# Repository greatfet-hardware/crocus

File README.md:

# Crocus
A GreatFET Neighbor for the 2.4 GHz wireless band.

Required KiCad dependency:

https://github.com/greatscottgadgets/gsg-kicad-lib

If you are using git, the preferred way to install gsg-kicad-lib is to use the
submodule:

```
git submodule init && git submodule update
```

# Background

Crocus is based on the Nordic RF nRF24L01+ and was inspired by [The Next Hope Badge](http://goodfet.sourceforge.net/hardware/nhb12/).

A notable capability of nRF24L01+ is 2 Mbps FSK.  Many 2.4 GHz wireless transceiver ICs (including the CC2400 on Ubertooth One) only support FSK up to 1 Mbps.  See [Promiscuity is the nRF24L01+'s Duty](http://travisgoodspeed.blogspot.com/2011/02/promiscuity-is-nrf24l01s-duty.html) for an excellent trick that can be done with Crocus.

## Usage Instructions

FIXME: We don't have any firmware yet, but we should implement capabilities similar to goodfet.nrf.

## Pin Usage

signal  | pin     | alt1  | alt2
--------|---------|-------|-----
SCK     | J1.38   | J2.32 |
COPI    | J1.39   | J2.30 |
CIPO    | J1.40   | J2.38 |
CSN     | via I2C | J1.37 | J1.29
CE      | via I2C | J2.9  | J2.21
SDA     | J2.39   |       |
SCL     | J2.40   |       |
INT     | J2.4    | J2.34 | J1.36

Alternative pins may be selected with solder jumpers.

## I2C Address

The default I2C address is 0x27.  Alternative addresses in the ranges 0x10-0x2F, 0x50-0x67, or 0x70-0x77 may be selected with solder jumpers.  Refer to the Crocus schematic and to the PCA9674 data sheet for details.

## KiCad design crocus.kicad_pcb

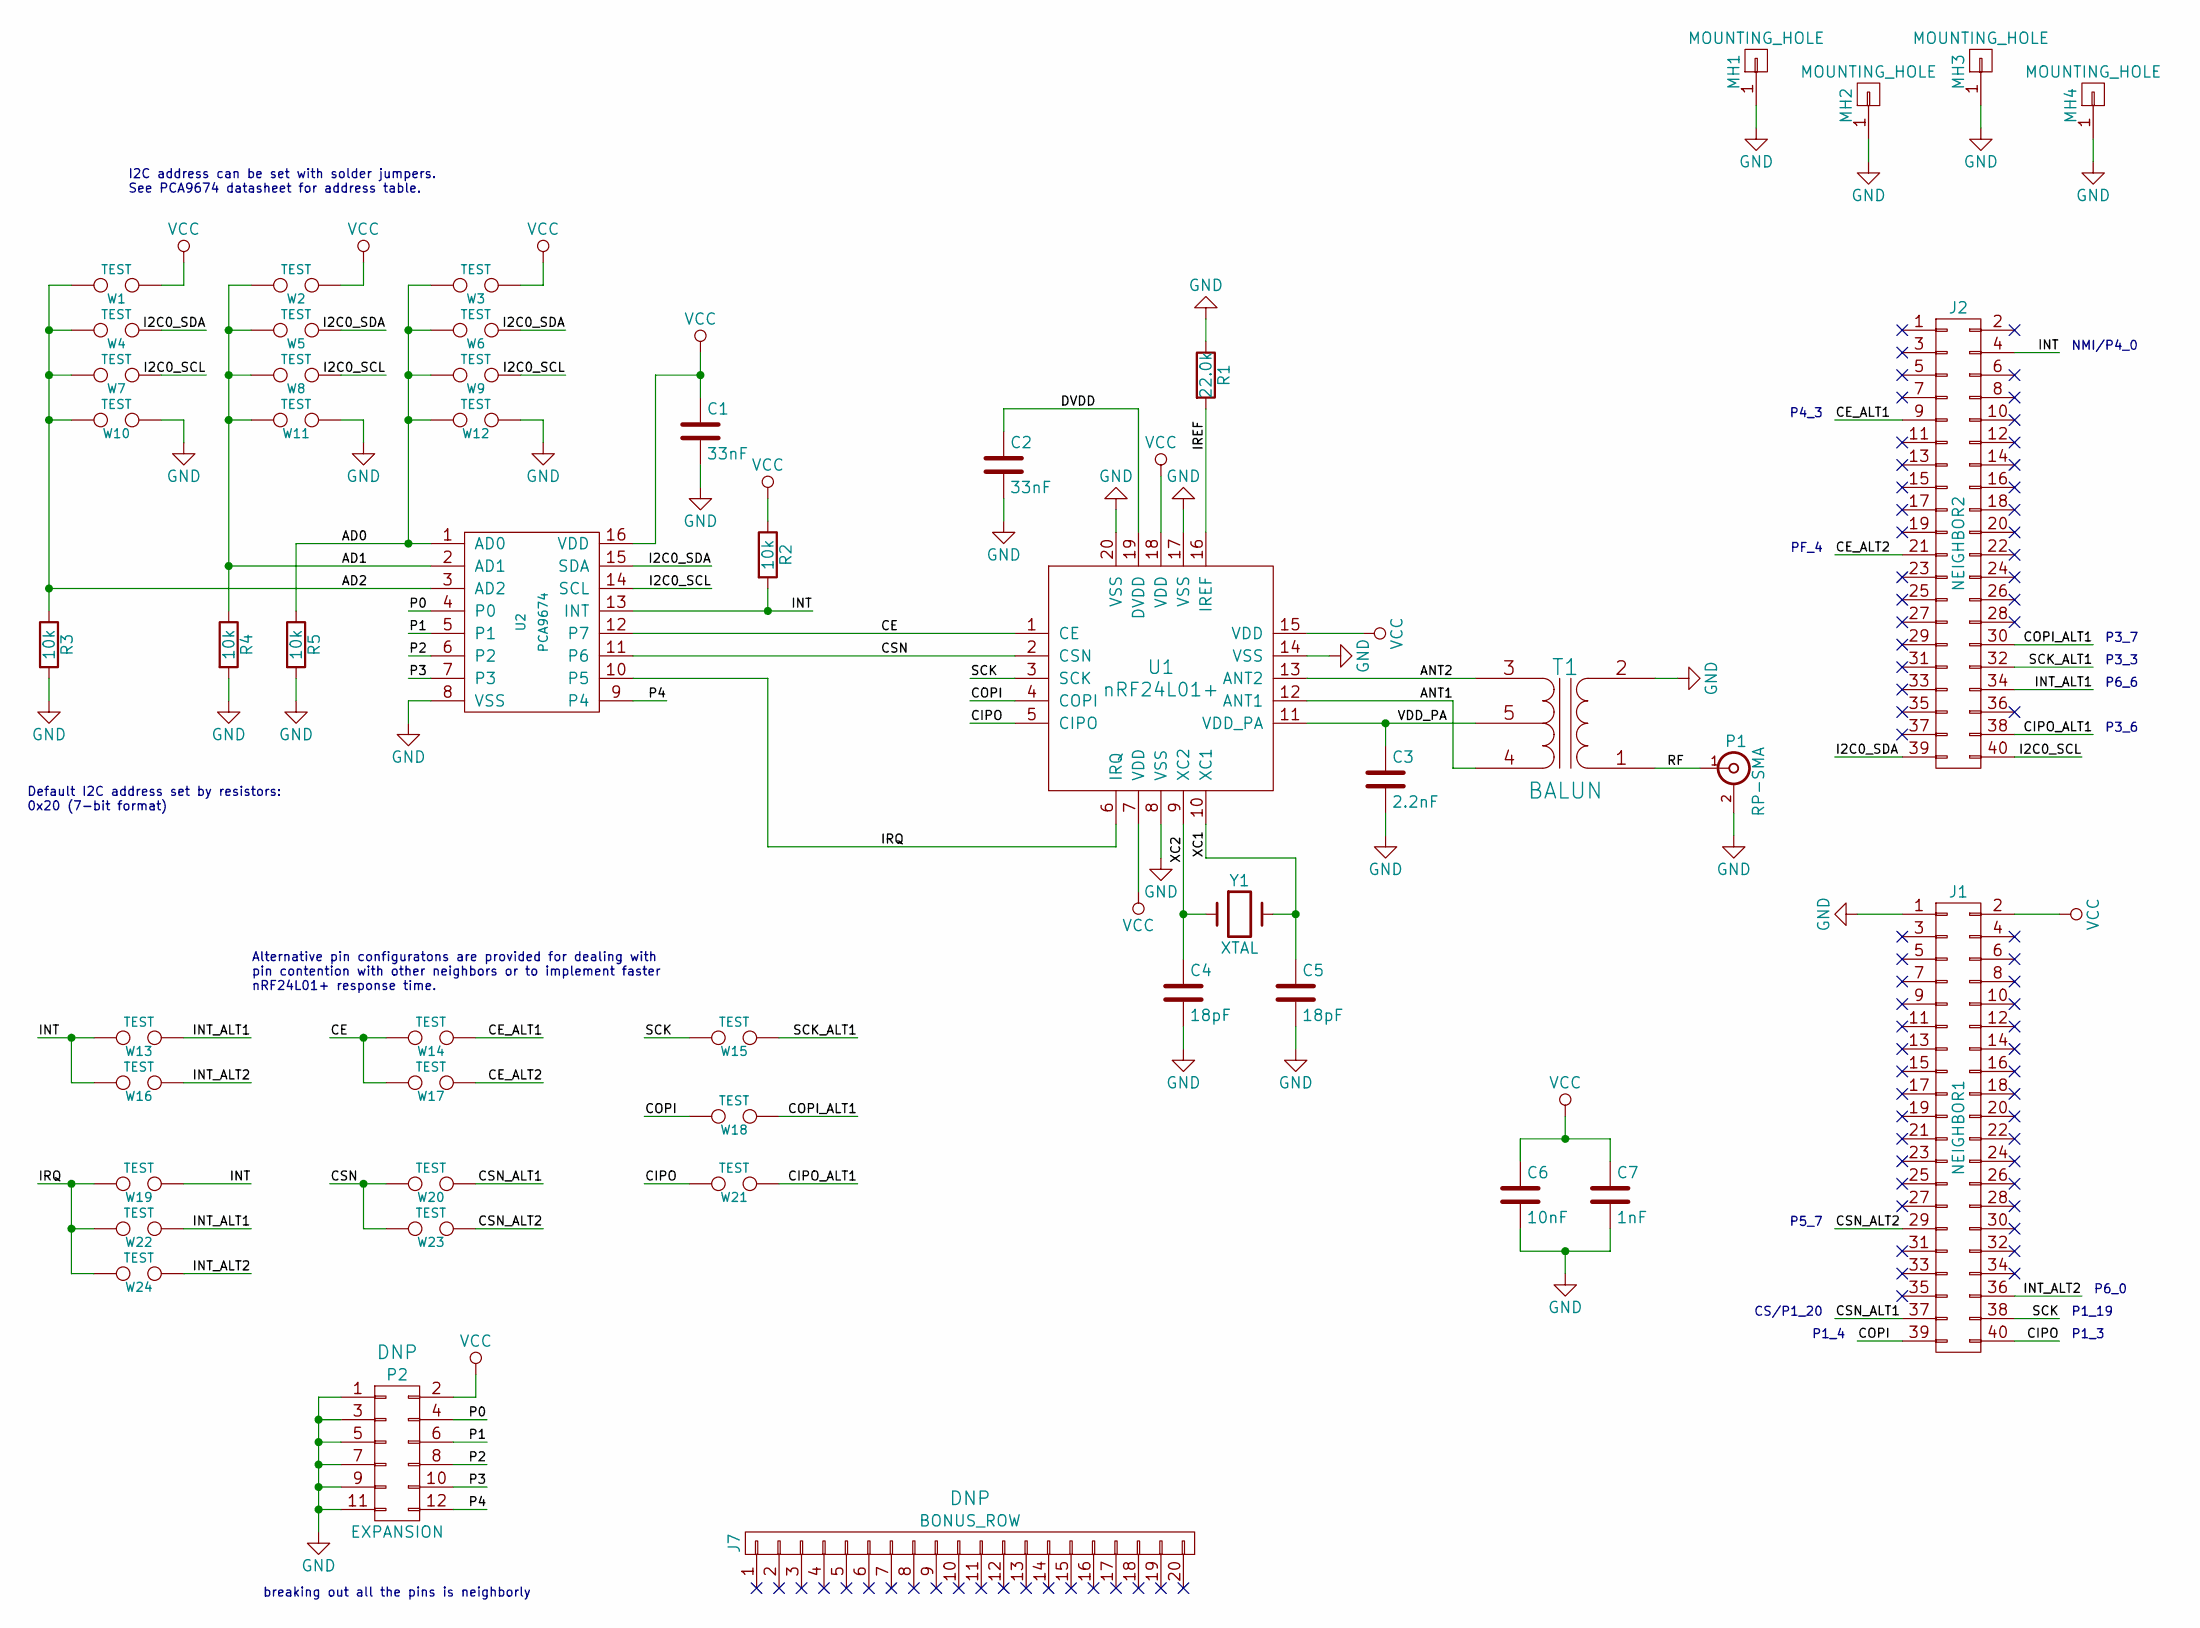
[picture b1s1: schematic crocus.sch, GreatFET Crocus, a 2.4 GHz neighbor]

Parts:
C1, C2: 33nF; 0603; Part Number CL10B333KB8SFNC
C3: 2.2nF; 0603; Part Number GRM188R71H222KA01D
C4, C5: 18pF; 0603; Part Number GRM1885C1H180JA01D
C6: 10nF; 0603; Part Number GRM188R71H103KA01D
C7: 1nF; 0603; Part Number GRM188R71H102KA01D
J1: NEIGHBOR1; HEADER-2x20; Part Number SSQ-120-23-G-D
J2: NEIGHBOR2; HEADER-2x20; Part Number SSQ-120-23-G-D
J7: BONUS_ROW; HEADER-1x20; Part Number SSQ-120-23-G-S
MH1, MH2, MH3, MH4: MOUNTING_HOLE; HOLE126MIL-COPPER
P1: RP-SMA; SMA-EDGE; Part Number CONREVSMA003.031
P2: EXPANSION; HEADER-2x6
R1: 22.0k; 0603; Part Number RMCF0603FT22K0
R2, R3, R4, R5: 10k; 0603; Part Number ERJ-3GEYJ103V
T1: BALUN; 2500BL14M100; Part Number 2450BM14A0002T
U1: nRF24L01+; QFN20-4; Part Number NRF24L01P-R7
U2: PCA9674; TSSOP16; Part Number PCA9674PW,118
W1, W2, W3, W4, W5, W6, W7, W8, W9, W10, W11, W12, W13, W14, W15, W16, W17, W18, W19, W20, W21, W22, W23, W24: TEST; 0603-JUMPER
Y1: XTAL; HC-49S; Part Number 9C-16.000MAAE-T

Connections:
/AD0: R5.1, U2.1 (AD0), W3.2, W6.2, W9.2, W12.2
/AD1: R4.1, U2.2 (AD1), W2.2, W5.2, W8.2, W11.2
/AD2: R3.1, U2.3 (AD2), W1.2, W4.2, W7.2, W10.2
/ANT1: T1.4 (PR2), U1.12 (ANT1)
/ANT2: T1.3 (PR1), U1.13 (ANT2)
/CE: U1.1 (CE), U2.12 (P7), W14.2, W17.2
/CE_ALT1: J2.9, W14.1
/CE_ALT2: J2.21, W17.1
/CIPO: J1.40, U1.5 (CIPO), W21.2
/CIPO_ALT1: J2.38, W21.1
/COPI: J1.39, U1.4 (COPI), W18.2
/COPI_ALT1: J2.30, W18.1
/CSN: U1.2 (CSN), U2.11 (P6), W20.2, W23.2
/CSN_ALT1: J1.37, W20.1
/CSN_ALT2: J1.29, W23.1
/DVDD: C2.1, U1.19 (DVDD)
/I2C0_SCL: J2.40, U2.14 (SCL), W7.1, W8.1, W9.1
/I2C0_SDA: J2.39, U2.15 (SDA), W4.1, W5.1, W6.1
/INT: J2.4, R2.2, U2.13 (INT), W13.2, W16.2, W19.1
/INT_ALT1: J2.34, W13.1, W22.1
/INT_ALT2: J1.36, W16.1, W24.1
/IREF: R1.2, U1.16 (IREF)
/IRQ: U1.6 (IRQ), U2.10 (P5), W19.2, W22.2, W24.2
/P0: P2.4, U2.4 (P0)
/P1: P2.6, U2.5 (P1)
/P2: P2.8, U2.6 (P2)
/P3: P2.10, U2.7 (P3)
/P4: P2.12, U2.9 (P4)
/RF: P1.1 (In), T1.1 (S1)
/SCK: J1.38, U1.3 (SCK), W15.2
/SCK_ALT1: J2.32, W15.1
/VDD_PA: C3.1, T1.5 (PM), U1.11 (VDD_PA)
/XC1: C5.1, U1.10 (XC1), Y1.2
/XC2: C4.1, U1.9 (XC2), Y1.1
GND: C1.2, C2.2, C3.2, C4.2, C5.2, C6.2, C7.2, J1.1, MH1.1, MH2.1, MH3.1, MH4.1, P1.2 (Ext), P2.1, P2.3, P2.5, P2.7, P2.9, P2.11, R1.1, R3.2, R4.2, R5.2, T1.2 (S2), U1.8 (VSS), U1.14 (VSS), U1.17 (VSS), U1.20 (VSS), U2.8 (VSS), W10.1, W11.1, W12.1
VCC: C1.1, C6.1, C7.1, J1.2, P2.2, R2.1, U1.7 (VDD), U1.15 (VDD), U1.18 (VDD), U2.16 (VDD), W1.1, W2.1, W3.1

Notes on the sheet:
P1_3
P1_4
P1_19
CS/P1_20
breaking out all the pins is neighborly
I2C address can be set with solder jumpers. See PCA9674 datasheet for address table.
Default I2C address set by resistors: 0x20 (7-bit format)
NMI/P4_0
P6_0
P3_3
P3_7
P3_6
P6_6
P4_3
PF_4
P5_7
Alternative pin configuratons are provided for dealing with pin contention with other neighbors or to implement faster nRF24L01+ response time.

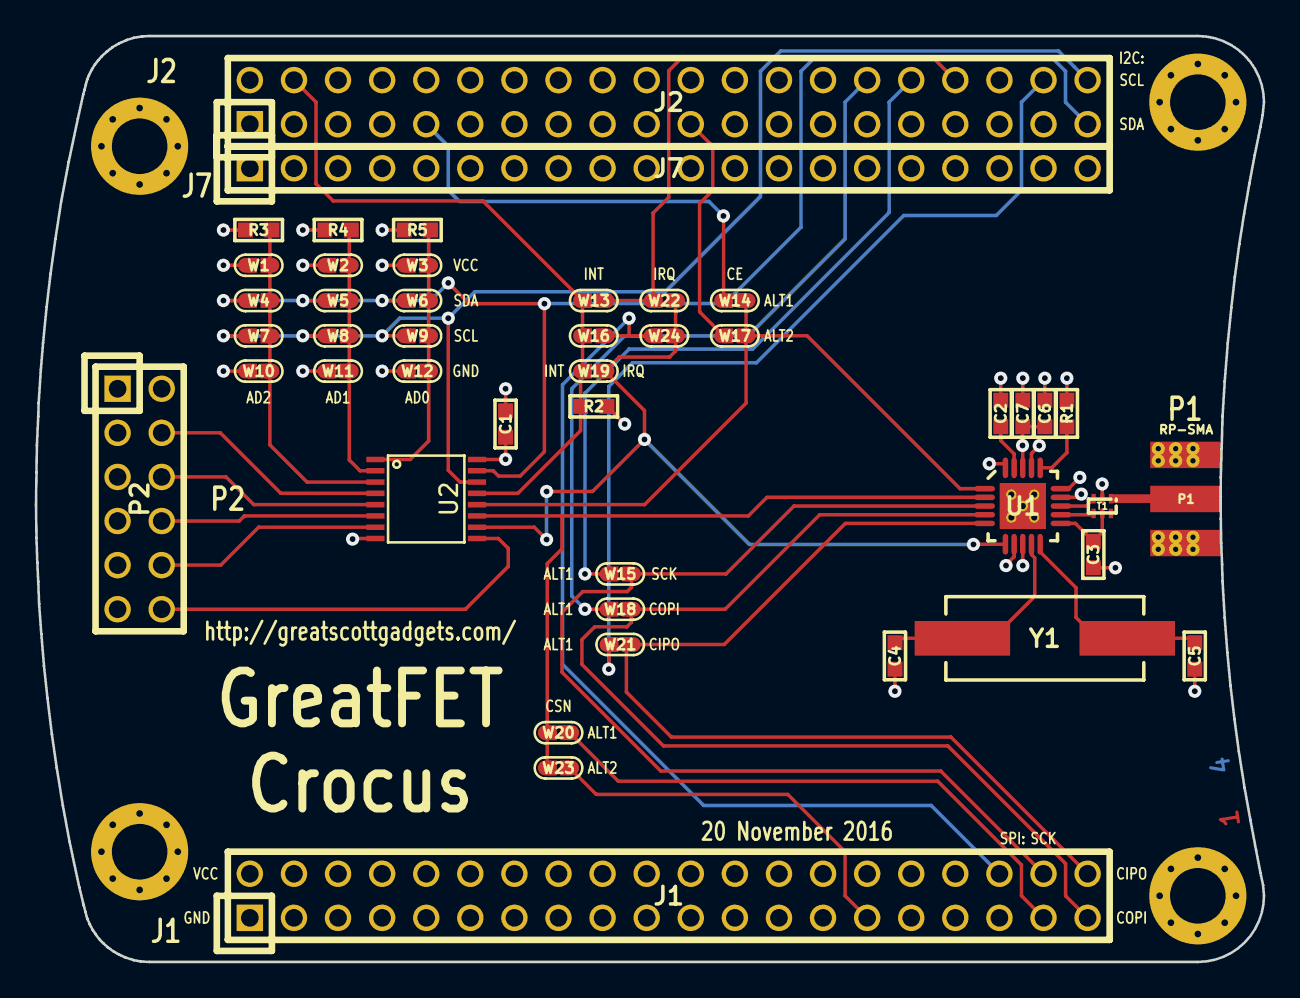
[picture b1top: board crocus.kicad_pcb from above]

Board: 4 copper layers, 70.7 x 53.3 mm, 49 parts (0 on the bottom side), 36 nets.

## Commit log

2019-05-27 split crocus into separate repository
2019-05-27 updated title in README.md
2019-09-06 move information from greatfet wiki to README
2019-10-10 Updated design for kicad 5.
2019-10-10 Changed I2C address to 0x27
2020-07-03 adopt OSHWA convention for SPI signal names https://www.oshwa.org/a-resolution-to-redefine-spi-signal-names
2020-07-03 reversed change to cached symbol library to avoid mismatch with library
2021-11-01 Update README to reflect I2C address change.
    PR #2 changed the I2C address of Crocus from 0x20 to 0x27.

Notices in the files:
crocus.sch:
Copyright 2015 Michael Ossmann
License: GPL v2
